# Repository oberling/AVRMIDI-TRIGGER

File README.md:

AVRMIDI-TRIGGER
==========

This is an implementation of a simple MIDI to Trigger converter using a Atmel Attiny2313 microprocessor. Each Note-On Event in a given MIDI Note Range is converted into a Trigger Signal of 5 V.

The current Note Range is 8 Notes from middle C (MIDI-Channel 5 - see Makefile for more info).
I was able to reuse a lot of sourcecode from my AVR MIDI-CV converter here... which is nice.

It also supports multitrigger/flames via velocity: there are 16 pre-defined flame pattern and velocity of 127 gives you a simple trigger.

If you want to see the MIDI to Trigger converter in action (also hearing the flame pattern): [video of the SDSV clone i built](https://www.youtube.com/watch?v=ALU4drFba9A)

Schematic
=========

Teststatus
==========

complete.

The code has been tested with my SDS5 clone and works fine.
The code has been tested with an oscilloscope and seems to work fine.

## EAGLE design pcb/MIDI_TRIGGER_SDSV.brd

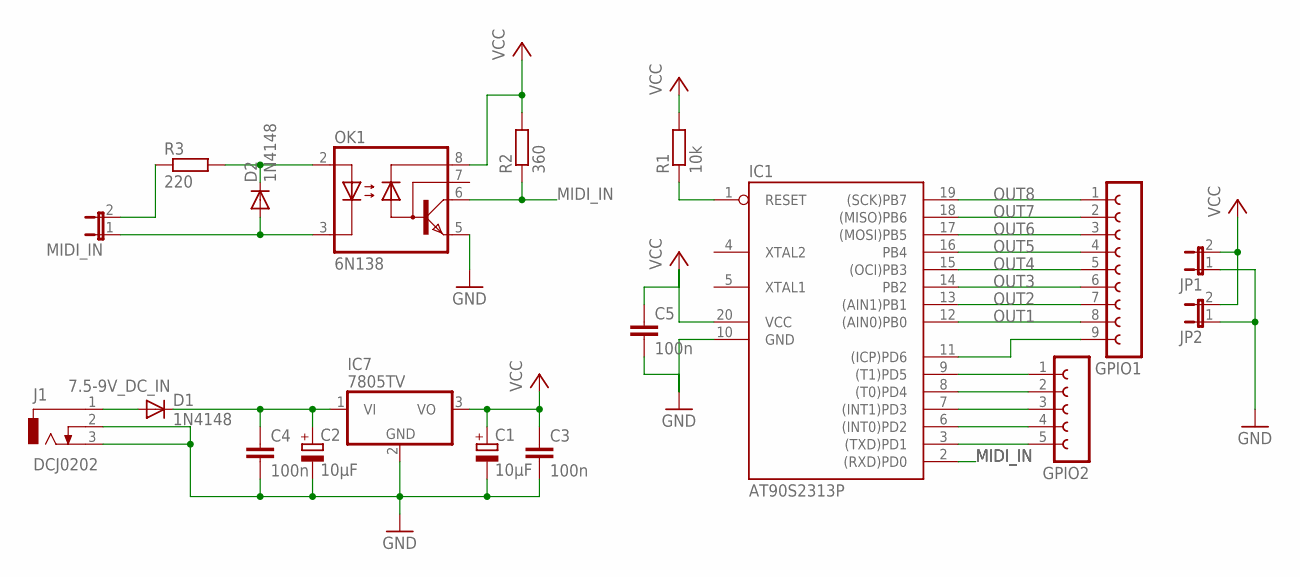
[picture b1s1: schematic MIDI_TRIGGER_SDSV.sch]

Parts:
C1, C2: 10µF; E5-8,5
C3, C4, C5: 100n; C050-025X075
D1, D2: 1N4148; DO35-7
GPIO1: FE09-1; FE09
GPIO2: FE05-1
IC1: AT90S2313P; DIL20
IC7: 7805TV; TO220V
J1: DCJ0202
JP1, JP2: JP1E; JP1
MIDI_IN: JP1E; JP1
OK1: 6N138; DIL08
R1: 10k; 0204/7
R2: 360; 0204/7
R3: 220; 0204/7

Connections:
7.5-9V_DC_IN: D1.A, J1.1
GND: C1.-, C2.-, C3.2, C4.2, C5.2, IC1.10 (GND), IC7.2 (GND), J1.2, J1.3, JP1.1, JP2.1, OK1.5 (GND)
MIDI_IN: IC1.2 ((RXD)PD0), OK1.6 (VO), R2.1
unnamed: GPIO1.9, IC1.11 ((ICP)PD6)
unnamed: GPIO2.1, IC1.9 ((T1)PD5)
unnamed: GPIO2.2, IC1.8 ((T0)PD4)
unnamed: C2.+, C4.1, D1.C, IC7.1 (VI)
unnamed: GPIO2.3, IC1.7 ((INT1)PD3)
unnamed: GPIO2.4, IC1.6 ((INT0)PD2)
unnamed: GPIO2.5, IC1.3 ((TXD)PD1)
unnamed: IC1.1 (RESET), R1.1
unnamed: MIDI_IN.2, R3.1
unnamed: D2.C, OK1.2 (A), R3.2
unnamed: D2.A, MIDI_IN.1, OK1.3 (C)
OUT1: GPIO1.8, IC1.12 ((AIN0)PB0)
OUT2: GPIO1.7, IC1.13 ((AIN1)PB1)
OUT3: GPIO1.6, IC1.14 (PB2)
OUT4: GPIO1.5, IC1.15 ((OCI)PB3)
OUT5: GPIO1.4, IC1.16 (PB4)
OUT6: GPIO1.3, IC1.17 ((MOSI)PB5)
OUT7: GPIO1.2, IC1.18 ((MISO)PB6)
OUT8: GPIO1.1, IC1.19 ((SCK)PB7)
VCC: C1.+, C3.1, C5.1, IC1.20 (VCC), IC7.3 (VO), JP1.2, JP2.2, OK1.8 (VCC), R1.2, R2.2

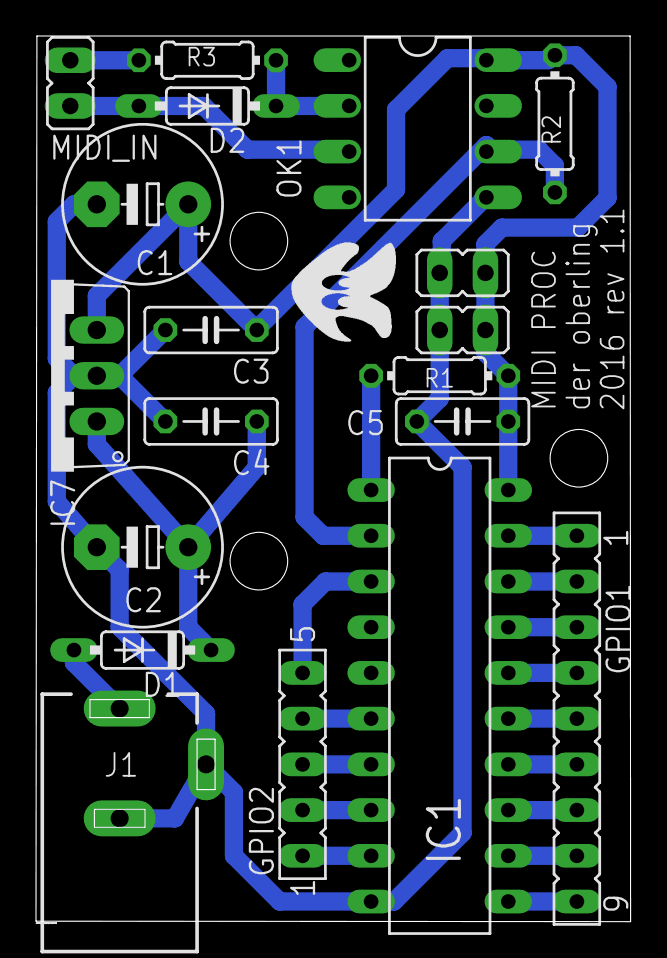
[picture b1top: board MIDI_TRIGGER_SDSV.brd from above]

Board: 2 copper layers, 33.0 x 49.2 mm, 19 parts (0 on the bottom side), 23 nets.

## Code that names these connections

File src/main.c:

#include "uart.h"
#include "midi_datatypes.h"
#include "midibuffer.h"
#include "trigger_flame.h"
#include <avr/io.h>
#include <avr/interrupt.h>
#include <avr/pgmspace.h>
#include <stdint.h>
#include <stdbool.h>

#define TRIGGER_PORT	PORTB
#define TRIGGER_DDR		DDRB
#define TRIGGER1		PB0
#define TRIGGER2		PB1
#define TRIGGER3		PB2
#define TRIGGER4		PB3
#define TRIGGER5		PB4
#define TRIGGER6		PB5
#define TRIGGER7		PB6
#define TRIGGER8		PB7
#define TRIGGER_PIN_OFFSET	0
#define NUM_TRIGGER_OUTPUTS		8
#ifndef TRIGGER_COUNTER_INIT
#pragma message "TRIGGER_COUTNER_INIT not defined - defaulting to 20"
#define TRIGGER_COUNTER_INIT	20
#endif
#ifndef MIDI_NOTE_OFFSET
#pragma message "MIDI_NOTE_OFFSET not defined - defaulting to 60"
// 60 is the middle C
#define MIDI_NOTE_OFFSET	60
#endif
#ifndef MIDI_CHANNEL
#pragma message "MIDI_CHANNEL not defined - defaulting to 5"
// MIDI_CHANNEL is off by 1 (begins at 0 but shown as 1)
#define MIDI_CHANNEL 4
#endif

#define TRIGGER_FLAME_PRESCALER	4

midibuffer_t midi_buffer;
uint8_t midi_channel = MIDI_CHANNEL;
uint8_t trigger_flame_counter = TRIGGER_FLAME_PRESCALER;

trigger_output_t trigger_output[NUM_TRIGGER_OUTPUTS];
bool must_update_trigger_output = false;

bool must_update_flames = false;

bool midi_handler_function(midimessage_t* m);
void update_trigger_output(void);
void update_flames(void);
void init_trigger_outputs(void);
void init_io(void);
void init_variables(void);

bool midi_handler_function(midimessage_t* m) {
	// only return true if something of interest happened
	if(m->byte[0] == NOTE_ON(midi_channel) && m->byte[2] != 0) { // Velocity must not be 0
		if(m->byte[1]>=MIDI_NOTE_OFFSET && m->byte[1]<(MIDI_NOTE_OFFSET+NUM_TRIGGER_OUTPUTS)) { // if in range of triggering notes
			trigger_output[m->byte[1]-MIDI_NOTE_OFFSET].output_counter = TRIGGER_COUNTER_INIT;
			// use velocity for flame selection - 127 being the normal single trigger
			uint8_t flame_type = m->byte[2]>>3; // simple scale down division by 8
			trigger_output[m->byte[1]-MIDI_NOTE_OFFSET].flame_type = flame_type;
			trigger_output[m->byte[1]-MIDI_NOTE_OFFSET].flame_sequence_position = 0;
			trigger_output[m->byte[1]-MIDI_NOTE_OFFSET].flame_sequence_counter = pgm_read_byte(&(trigger_flame[flame_type][0]));
			return true;
		}
	}
	return false;
}

void update_trigger_output(void) {
	// only change output status - no decrement of counters here!
	uint8_t i=0;
	for(;i<NUM_TRIGGER_OUTPUTS;i++) {
		if(trigger_output[i].output_counter) {
			TRIGGER_PORT |= (1<<(TRIGGER_PIN_OFFSET+i));
		} else {
			TRIGGER_PORT &= ~(1<<(TRIGGER_PIN_OFFSET+i));
		}
	}
}

void update_flames(void) {
	uint8_t i=0;
	for(;i<NUM_TRIGGER_OUTPUTS;i++) {
		if(trigger_output[i].flame_sequence_counter) {
			// count down our current sequence counter
			trigger_output[i].flame_sequence_counter -= 1;
			// current sequence step is over - see if there are remaining steps
			if(
				trigger_output[i].flame_sequence_counter == 0 &&
				trigger_output[i].flame_sequence_position < NUM_FLAME_STEPS-1 && 
				pgm_read_byte(&(trigger_flame[trigger_output[i].flame_type][trigger_output[i].flame_sequence_position+1]))
			) {
					// initiate next step of sequence - trigger the output
					trigger_output[i].flame_sequence_position += 1;
					trigger_output[i].flame_sequence_counter = pgm_read_byte(&(trigger_flame[trigger_output[i].flame_type][trigger_output[i].flame_sequence_position]));
					trigger_output[i].output_counter = TRIGGER_COUNTER_INIT;
					must_update_trigger_output = true;
			}
		}
	}
}

void init_trigger_outputs(void) {
	uint8_t i=0;
	for(;i<NUM_TRIGGER_OUTPUTS;i++) {
		trigger_output[i].output_counter = 0;
		trigger_output[i].flame_sequence_position = 0;
		trigger_output[i].flame_sequence_counter = 0;
		trigger_output[i].flame_type = 0;
	}
}

void init_io(void) {
	TRIGGER_DDR |= (1<<TRIGGER1)|(1<<TRIGGER2)|(1<<TRIGGER3)|(1<<TRIGGER4)|(1<<TRIGGER5)|(1<<TRIGGER6)|(1<<TRIGGER7)|(1<<TRIGGER8);
	TCCR0B = (1<<CS01); // at 8000000Hz/8 = 1000000Hz -> 1000000Hz/256 = 3906.25Hz -> 1/3906.25Hz = 256µs
	TIMSK |= (1<<TOIE0);
	uart_init();
}

void init_variables(void) {
	midibuffer_init(&midi_buffer, &midi_handler_function);
	init_trigger_outputs();
}

ISR(TIMER0_OVF_vect) {
	// decrement counters here - trigger update of outputs if trigger is over
	uint8_t i=0;
	for(;i<NUM_TRIGGER_OUTPUTS;i++) {
		if(trigger_output[i].output_counter) {
			trigger_output[i].output_counter -= 1;
			if(trigger_output[i].output_counter == 0) {
				must_update_trigger_output = true;
			}
		}
	}
	trigger_flame_counter++;
	if(trigger_flame_counter > TRIGGER_FLAME_PRESCALER) {
		trigger_flame_counter = 0;
		must_update_flames = true;
	}
}

ISR(USART_RX_vect) {
	char a;
	uart_getc(&a);
	// this method only affects the writing position in the midibuffer
	// therefor it's ISR-save as long as the buffer does not run out of
	// space!!! prepare your buffers, everyone!
	midibuffer_put(&midi_buffer, a);
}

int main(int argc, char** argv) {
	cli();
	init_variables();
	init_io();
	sei();
	while(true) {
		// handle midi data prefered - always handle all midi messages first
		while(midibuffer_tick(&midi_buffer)) {
			must_update_trigger_output = true;
		}
		if(must_update_trigger_output) {
			must_update_trigger_output = false;
			update_trigger_output();
		}
		if(must_update_flames) {
			// could be done in the interrupt routine as well but has too many instructions
			must_update_flames = false;
			update_flames();
		}
	}
	return 0;
}

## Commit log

2016-02-07 initial commit - tested to work on attiny2313
2016-02-07 added fusebitsettings
2016-02-07 added MIDI_NOTE_OFFSET to Makefile and explained TRIGGER_COUNTER_INIT
2016-02-07 added some comments to clarify the code
2016-02-07 removed unnecessary definitions
2016-02-07 corrected UBRR calculation
2016-02-11 added multitrigger for flaming drum effects
2016-02-11 made MIDI_CHANNEL a Makefile definition
2016-02-11 added some compiling flags for better memory tracing
2016-02-11 save us 4 precious bytes of flash memory :)
2016-02-11 added note about new multitrigger/flame feature
2016-02-14 added (generic) pcb and schematic
2016-02-14 also added easy printable pcb png for home etching
2016-02-14 removed unnecessary DDR command
2016-07-31 always handle all MIDI-data before doing anything else
2016-07-31 updated README - teststatus complete and MIDICHANNEL is 5
2016-11-03 generalizing to 8 outputs
2016-11-03 added video link to README
2017-03-12 rewritten midibuffer handling
2017-03-20 added some initializations
2017-03-20 removed unnecessary functions and reimplemented midibuffer
2017-03-27 updated schematic and added picture of schematic for non-eagle users
